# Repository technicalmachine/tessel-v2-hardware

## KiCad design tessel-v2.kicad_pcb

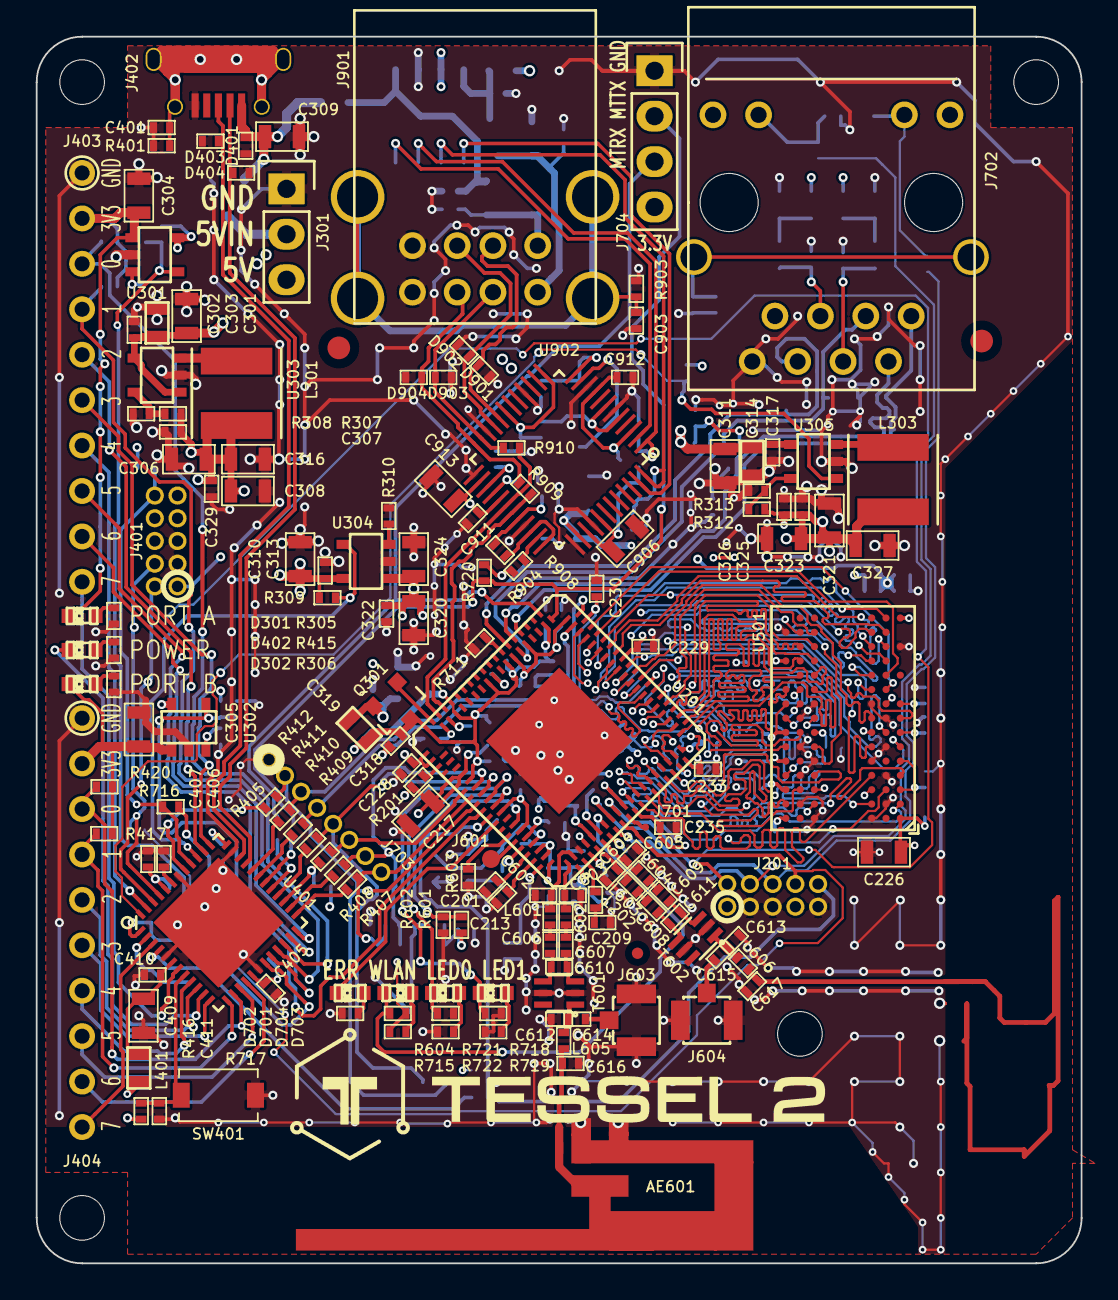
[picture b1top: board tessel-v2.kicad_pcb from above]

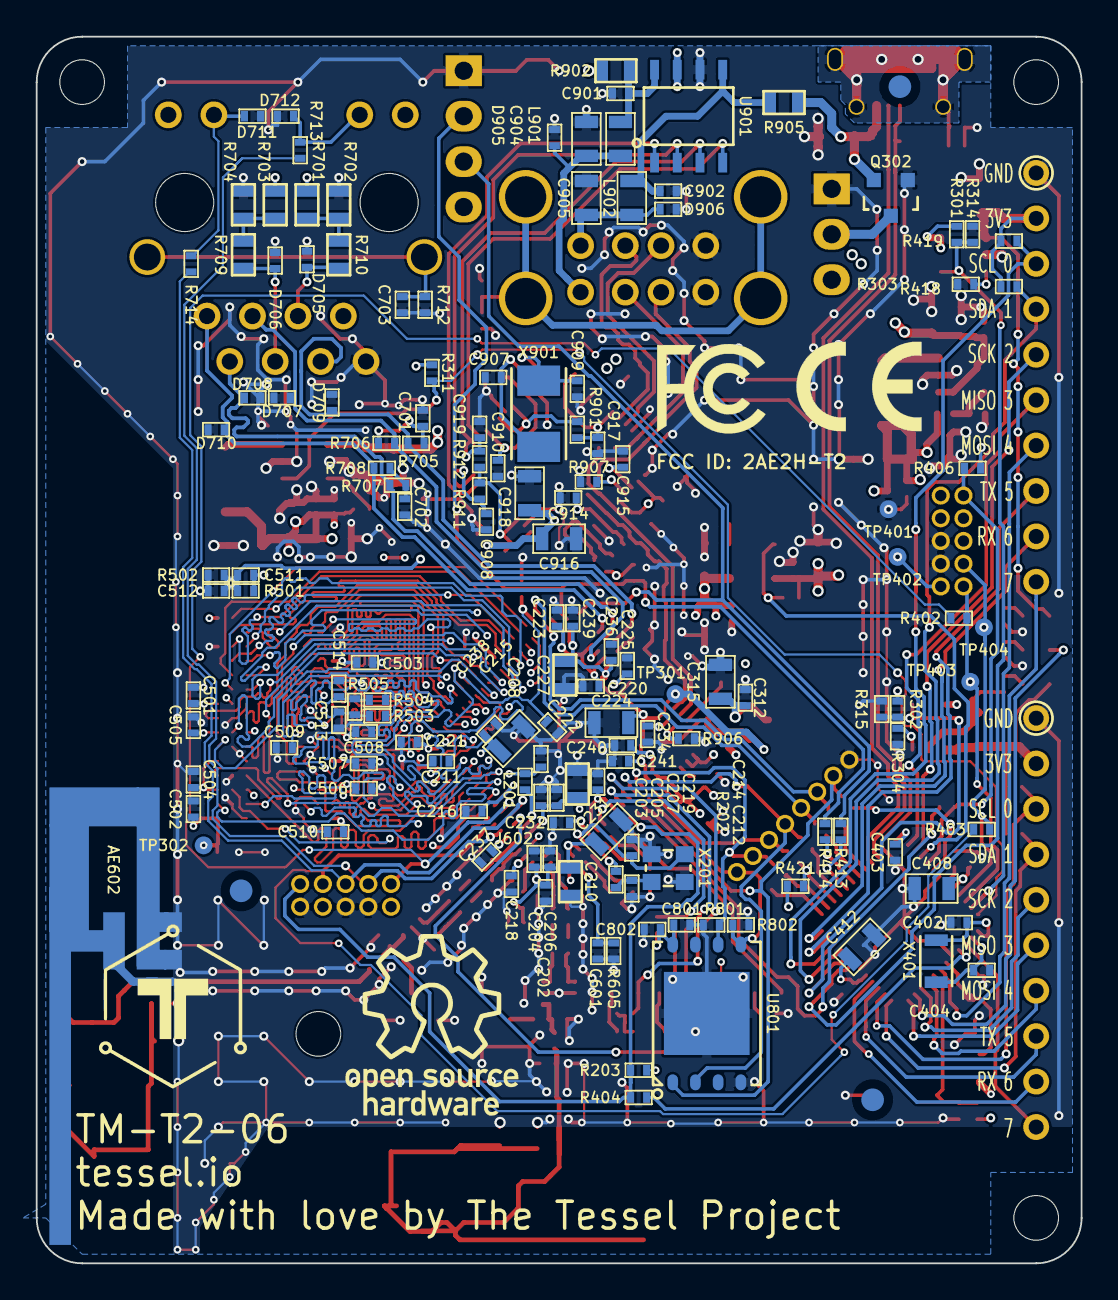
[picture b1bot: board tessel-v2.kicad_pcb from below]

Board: 4 copper layers, 58.4 x 68.6 mm, 315 parts (151 on the bottom side), 201 nets.

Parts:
AE601, AE602: ANTENNA; 2.4GHz-INVERTED-F-ANTENNA
C201, C208, C209, C220, C230, C238, C325, C329, C406, C908, C919: 1uF; SMD-0402-C
C202, C203, C204, C402, C404: 10pF; SMD-0402-C
C205, C206, C211, C216, C218, C219, C221, C222, C223, C225, C228, C229, C232, C233, C234, C235, C236, C237, C239, C240, C241, C307, C312, C318, C322, C326, C403, C405, C407, C410, C411, C502, C503, C504, C505, C507, C508, C509, C510, C511, C512, C701, C702, C801, C802, C901, C902, C910, C911, C912, C914, C915, C917: 100nF; SMD-0402-C
C207, C210, C227, C303, C314, C319: 4.7uF; SMD-0603-C
C212, C214, C907, C909: 18pF; SMD-0402-C
C213, C302, C313, C317, C501, C506: 10nF; SMD-0402-C
C215, C217, C224, C226, C308, C324, C327: 10uF DNP; SMD-0805-C
C231, C301, C304, C305, C306, C309, C310, C311, C315, C316, C320, C321, C323, C408, C409, C412, C904, C905, C906, C913, C916, C918: 10uF; SMD-0805-C
C401, C601, C606, C607, C608, C609, C703, C903: 100pF; SMD-0402-C
C513, C514: 5pF; SMD-0402-C
C602, C603, C604, C605: 2.2pF; SMD-0402-C
C610, C611: 0.8pF; SMD-0402-C
C612, C613, C616, C617: 1.8pF; SMD-0402-C
C614, C615: 100pF DNP; SMD-0402-C
D301, D302, D704: GREEN; LED-0603
D401, D403, D404, D901, D902, D903, D904, D905, D906: CV0402VT6030T; SMD-0402-R
D402, D703: BLUE; LED-0603
D701: AMBER; LED-0603
D702: RED; LED-0603
D705, D706, D707, D708, D709, D710, D711, D712: CV0402VT6001T; SMD-0402-R
F101, F102, F103, F104, F105, F106: fiducial
H101, H102, H103, H104: HOLE; MountingHole_2-5mm
J201, J401: CONN_02X05 DNP; CONN_02x05_0.05in
J301: CONN_01X03 DNP; Pin_Header_Straight_1x03
J402: MICROUSB-TH; Seeed-USB-Micro-320010028
J403, J404: MODULE_HEADER; MODULE_HEADER_TESSEL-backside
J601, J602, J701: CONN_01X01; Testpoint
J603, J604: UFL DNP; 1909763-1
J702: HR911105A; RB1-125BAG1A
J703: CONN_01X08 DNP; CONN_01x08_0.05in
J704: CONN_01X04 DNP; Pin_Header_Straight_1x04
J901: USB_A_2_stack; Molex-0672983090
L201, L202: 3.9nH; SMD-0402-R
L301, L303: 2.2uH; SWPA5020S
L401: 10uH; SMD-0603-R
L601, L602, L603, L604: 3nH; SMD-0402-R
L605, L606: 2.4nH; SMD-0402-R
L901, L902: BLM21PG221SN1D; SMD-0805-R
Q301: MMSS8550; SOT23
Q302: DMG2305UX; SOT-23
R201, R203, R417, R418, R419, R420, R601, R603, R720, R801, R802: 4.7kR; SMD-0402-R
R202, R404, R405, R407, R408, R409, R410, R411, R412, R413, R414, R503, R504, R716: 22R; SMD-0402-R
R301, R302: 100kR DNP; SMD-0402-R
R303, R304: 27kR; SMD-0402-R
R305, R306, R505, R722: 120R; SMD-0402-R
R307: 450kR 1%; SMD-0402-R
R308, R313: 100kR 1%; SMD-0402-R
R309, R310, R311, R406, R416, R421, R904, R908: 10kR; SMD-0402-R
R312: 200kR 1%; SMD-0402-R
R314, R315, R401, R604, R712, R718, R721, R901, R903: 100kR; SMD-0402-R
R402, R403, R713, R714, R715: 330R; SMD-0402-R
R415, R717, R719: 1kR; SMD-0402-R
R501, R502: 4.7kR 1%; SMD-0402-R
R602: 4.7kR DNP; SMD-0402-R
R605: 24kR 1%; SMD-0402-R
R701, R702, R703, R704: 10kR DNP; SMD-0603-R
R705, R706, R707, R708: 49.9R 1%; SMD-0402-R
R709, R710: 100kR DNP; SMD-0603-R
R711: 6.19kR 1%; SMD-0402-R
R902, R905: 0R DNP; SMD-0603-R
R906: 8.2kR 1%; SMD-0402-R
R907: 2.7kR 1%; SMD-0402-R
R909, R910: 0R DNP; SMD-0402-R
R911, R912: 450kR; SMD-0402-R
SILK101: Tessel 2 logo; TESSEL-TEXT-LOGO-31.8mm8.1mm
SILK102: OSHW logo; OSHW-Silk
SILK103: Tessel logo; Tessel-logo-10_2mm
SILK104: Tessel logo; LOGO-CE-5mm
SILK105: Tessel logo; LOGO-FCC-5mm
SW401: SW_PUSH; TL1015AF160QG
T601, T602: 2450BL15B100; EIA-0805
TP301, TP302, TP401, TP402, TP403, TP404: TP; Testpoint
U201: MT7620N
U301, U302, U304: MT9700; SOT-23-5
U303, U305: AP3418; SOT-23-5
U401: SAMD21G17A-MU; QFN-48-1EP-7mm
U501: W9751G6KB-25; WBGA-84
U801: S25FL256SAGNFI001; WNG008
U901: AIC1528-0PSTR; SOP-8
U902: FE1.1; CY7C65634-48AXCT
X201: 20MHz; CTS-425
X401: FC-135
X901: 12MHz; Seeed-xtal-12MHz

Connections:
3.3V_CP: C306.1, C307.1, C308.1, C310.1, C313.1, C316.1, C329.1, C403.1, C405.1, C407.1, C408.1, C412.1, J401.1, L301.1, L401.1, R301.1, R302.1, R307.1, R309.1, R406.2, R416.2, R421.2, TP402.~, U301.5, U302.5, U304.5, U401.17, U401.36, U401.44
3.3V_PORTA: C304.1, D301.2, J403.2, R418.2, R419.2, U301.1
3.3V_PORTB: C305.1, D302.2, J404.2, R417.2, R420.2, U302.1
12S_CTRL: Q301.1, U201.54
18V_EN: R311.2, U305.1, U401.48
+1.2V: C216.1, C219.1, C222.1, C224.1, C227.1, C230.1, C233.1, C236.1, C239.1, C241.1, C318.1, C319.1, Q301.3, TP301.~, U201.18, U201.25, U201.35, U201.51, U201.55, U201.84, U201.114, U201.120, U201.123, U201.128, U201.135, U201.140, U201.143
+1.8V: C215.1, C218.1, C221.1, C226.1, C229.1, C232.1, C235.1, C238.1, C312.1, C315.1, C318.2, C319.2, C321.1, C323.1, C325.1, C326.1, C327.1, C501.1, C502.1, C503.1, C504.1, C505.1, C506.1, C507.1, C508.1, C509.1, C510.1, C511.1, L303.1, Q301.2, R312.1, R501.2, TP302.~, U201.3, U201.10, U201.29, U201.93, U201.95, U201.144, U201.148, U501.A1, U501.A9, U501.C1, U501.C3, U501.C7, U501.C9, U501.E1, U501.E9, U501.G1, U501.G3, U501.G7, U501.G9, U501.J1, U501.J9, U501.M9, U501.R1
+3V3: C202.1, C203.1, C204.1, C205.1, C206.1, C207.1, C208.1, C209.1, C210.1, C217.1, C220.1, C223.1, C225.1, C228.1, C231.1, C234.1, C237.1, C240.1, C320.1, C322.1, C324.1, C801.1, C802.1, J201.1, J702.9, J702.12, J704.4, L201.1, L202.1, R201.2, R203.2, R311.1, R601.1, R604.1, R701.2, R703.2, R715.1, R720.1, R904.1, U201.1, U201.6, U201.56, U201.57, U201.60, U201.61, U201.79, U201.112, U201.117, U201.119, U201.122, U201.129, U201.134, U201.146, U201.147, U304.1, U801.8
+5V: C301.1, C302.1, C303.1, C309.1, C311.1, C314.1, C317.1, C916.1, C918.1, D401.1, J301.3, J402.1, Q302.2, R902.1, R905.1, U303.1, U303.4, U305.4, U901.7, U902.38
/COPROCESSOR/BUTTON: C411.1, R416.1, SW401.2, U401.8
/COPROCESSOR/CP_BRIDGE_MISO_SAM: R410.2, U401.28
/COPROCESSOR/CP_BRIDGE_MOSI_SAM: R407.2, U401.25
/COPROCESSOR/CP_BRIDGE_SAM_RX_SAM: R414.2, U401.30
/COPROCESSOR/CP_BRIDGE_SAM_TX_SAM: R413.2, U401.29
/COPROCESSOR/CP_BRIDGE_SCK_SAM: R408.2, U401.26
/COPROCESSOR/CP_BRIDGE_SCL_SAM: R412.2, U401.32
/COPROCESSOR/CP_BRIDGE_SDA_SAM: R411.2, U401.31
/COPROCESSOR/CP_BRIDGE_~CS~_SAM: R409.2, R421.1, U401.27
/COPROCESSOR/FLASH_~CS~_SAM: R405.1, U401.41
/COPROCESSOR/PORT_A_G1/TX: J403.8, U401.23
/COPROCESSOR/PORT_A_G2/RX: J403.9, U401.24
/COPROCESSOR/PORT_A_G3: J403.10, U401.7
/COPROCESSOR/PORT_A_MISO: J403.6, U401.37
/COPROCESSOR/PORT_A_MOSI: J403.7, U401.47
/COPROCESSOR/PORT_A_SCK: J403.5, U401.38
/COPROCESSOR/PORT_A_SCL: J403.3, R419.1, U401.22
/COPROCESSOR/PORT_A_SDA: J403.4, R418.1, U401.21
/COPROCESSOR/PORT_B_G1/TX: J404.8, U401.15
/COPROCESSOR/PORT_B_G2/RX: J404.9, U401.16
/COPROCESSOR/PORT_B_G3: J404.10, U401.3
/COPROCESSOR/PORT_B_MISO: J404.6, U401.12
/COPROCESSOR/PORT_B_MOSI: J404.7, U401.9
/COPROCESSOR/PORT_B_SCK: J404.5, U401.10
/COPROCESSOR/PORT_B_SCL: J404.3, R420.1, U401.14
/COPROCESSOR/PORT_B_SDA: J404.4, R417.1, U401.13
/COPROCESSOR/POWER_LED: D402.2, U401.11
/COPROCESSOR/SAM_USB_DM: D404.1, J402.2, U401.33
/COPROCESSOR/SAM_USB_DP: D403.1, J402.3, U401.34
/COPROCESSOR/SAM_USB_SHELL: C401.1, J402.6, J402.7, J402.8, J402.9, J402.10, J402.11, R401.1
/COPROCESSOR/SAM_XTAL32_1: C402.1, U401.1, X401.1
/COPROCESSOR/SAM_XTAL32_2: C404.1, U401.2, X401.2
/COPROCESSOR/VDDCORE: C406.1, U401.43
/COPROCESSOR/~PORST~_SAM: R404.1, U401.4
/MEDIATEK/MT_PLL_VC_CAP: C213.1, U201.73
/MEDIATEK/MT_XTAL_XI: C214.1, U201.145, X201.3
/MEDIATEK/MT_XTAL_XO: R202.1, U201.71
/MEDIATEK/MT_XTAL_XO_R: C212.1, R202.2, X201.1
/MEDIATEK/RF0_V33N: L201.2, U201.80
/MEDIATEK/RF1_V33N: L202.2, U201.2
/MEDIATEK_I/O/EPHY_RES: R711.1, U201.43
/MEDIATEK_I/O/ETH_LED_GREEN: D711.1, J702.11, R714.1
/MEDIATEK_I/O/ETH_LED_YELLOW: D712.1, J702.10, R713.1
/MEDIATEK_I/O/ETH_SHELL: C703.1, J702.13, J702.14, R712.1
/MEDIATEK_I/O/MT_GPIO_WP: R716.2, U201.65
/MEDIATEK_I/O/MT_~RESET: J701.1, U201.9
/MEDIATEK_I/O/RM: C701.1, R705.1, R706.1
/MEDIATEK_I/O/RN_P1: D709.1, J702.6, R705.2, U201.42
/MEDIATEK_I/O/RP_P1: D707.1, J702.3, R706.2, U201.118
/MEDIATEK_I/O/RXM: R701.1, R702.2, R710.2
/MEDIATEK_I/O/RX_MIDTAP: D705.1, J702.5, R710.1
/MEDIATEK_I/O/TM: C702.1, R707.1, R708.1
/MEDIATEK_I/O/TN_P1: D708.1, J702.2, R707.2, U201.41
/MEDIATEK_I/O/TP_P1: D710.1, J702.1, R708.2, U201.40
/MEDIATEK_I/O/TXM: R703.1, R704.2, R709.2
/MEDIATEK_I/O/TX_MIDTAP: D706.1, J702.4, R709.1
/MEDIATEK_I/O/USER_LED_BLUE: D703.2, R718.1, U201.138
/MEDIATEK_I/O/USER_LED_GREEN: D704.2, R721.1, U201.139
/POWER/5V_IN: J301.2, Q302.3
/POWER/18S_FB: R312.2, R313.1, U305.5
/POWER/18S_SW: L303.2, U305.3
/POWER/33C_FB: R307.2, R308.1, U303.5
/POWER/33C_SW: L301.2, U303.3
/RAM/A0: U201.20, U501.M8
/RAM/A1: U201.107, U501.M3
/RAM/A2: U201.96, U501.M7
/RAM/A3: U201.31, U501.N2
/RAM/A4: U201.21, U501.N8
/RAM/A5: U201.106, U501.N3
/RAM/A6: U201.97, U501.N7
/RAM/A7: U201.30, U501.P2
/RAM/A8: U201.22, U501.P8
/RAM/A9: U201.104, U501.P3
/RAM/A10: U201.32, U501.M2
/RAM/A11: U201.98, U501.P7
/RAM/A12: U201.105, U501.R2
/RAM/BA0: U201.33, U501.L2
/RAM/BA1: U201.108, U501.L3
/RAM/CKE: U201.34, U501.K2
/RAM/DDR2_CLK: C513.1, R503.1, R505.1, U501.J8
/RAM/DQ0: U201.24, U501.G8
/RAM/DQ1: U201.26, U501.G2
/RAM/DQ2: U201.99, U501.H7
/RAM/DQ3: U201.27, U501.H3
/RAM/DQ4: U201.102, U501.H1
/RAM/DQ5: U201.23, U501.H9
/RAM/DQ6: U201.101, U501.F1
/RAM/DQ7: U201.100, U501.F9
/RAM/DQ8: U201.88, U501.C8
/RAM/DQ9: U201.11, U501.C2
/RAM/DQ10: U201.87, U501.D7
/RAM/DQ11: U201.12, U501.D3
/RAM/DQ12: U201.86, U501.D1
/RAM/DQ13: U201.13, U501.D9
/RAM/DQ14: U201.85, U501.B1
/RAM/DQ15: U201.14, U501.B9
/RAM/DQM0: U201.28, U501.F3
/RAM/DQM1: U201.15, U501.B3
/RAM/DQS0: U201.103, U501.F7
/RAM/DQS1: U201.89, U501.B7
/RAM/M_DDR2_CLK: R503.2, U201.90
/RAM/M_~DDR2_CLK: R504.2, U201.16
/RAM/ODT: U201.17, U501.K9
/RAM/~CAS: U201.19, U501.L7
/RAM/~CS: U201.94, U501.L8
/RAM/~DDR2_CLK: C514.1, R504.1, R505.2, U501.K8
/RAM/~RAS: U201.92, U501.K7
/RAM/~WE: U201.109, U501.K3
/RF/ANT_TRN: R601.2, R602.2, U201.142
/RF/ANT_TRNB: R603.2, U201.69
/RF/NC_70: J601.1, U201.70
/RF/NC_78: J602.1, U201.78
/RF/RF0_BALUN_IN_N: C606.1, C610.1, T601.4
/RF/RF0_BALUN_IN_P: C607.1, C610.2, T601.3
/RF/RF0_BALUN_OUT: C612.1, C614.2, L605.2, T601.1
/RF/RF0_FEED: AE601.1, C616.1, L605.1
/RF/RF0_OUTN: C602.1, L601.2, U201.76
/RF/RF0_OUTN_TCIN: C606.2, L601.1
/RF/RF0_OUTP: C603.1, L602.2, U201.75
/RF/RF0_OUTP_TCIN: C607.2, L602.1
/RF/RF1_BALUN_IN_N: C609.1, C611.2, T602.3
/RF/RF1_BALUN_IN_P: C608.1, C611.1, T602.4
/RF/RF1_BALUN_OUT: C613.1, C615.2, L606.2, T602.1
/RF/RF1_FEED: AE602.1, C617.1, L606.1
/RF/RF1_OUTN: C605.1, L604.2, U201.5
/RF/RF1_OUTN_TCIN: C609.2, L604.1
/RF/RF1_OUTP: C604.1, L603.2, U201.4
/RF/RF1_OUTP_TCIN: C608.2, L603.1
/RF/UFL_0: C614.1, J603.1
/RF/UFL_1: C615.1, J604.1
/USB/33_USB: C906.1, C914.1, C915.1, C917.1, R901.1, R908.1, R911.1, R912.1, U902.13, U902.19, U902.27, U902.32, U902.39, U902.41
/USB/OVR#[1]: C908.1, R911.2, U901.2, U902.48
/USB/OVR#[2]: C919.1, R912.2, U901.3, U902.1
/USB/OVR#[3]: R901.2, U902.5, U902.7
/USB/PWR#[1]: U901.1, U902.47
/USB/PWR#[2]: U901.4, U902.2
/USB/UPHY0_PADM: R910.1, U201.53, U902.30
/USB/UPHY0_PADP: R909.1, U201.52, U902.31
/USB/UPHY0_VRES: R906.1, U201.130
/USB/USB_18: C910.1, C911.1, C912.1, C913.1, U902.3, U902.9, U902.26, U902.29
/USB/USB_DD+[1]: D904.1, J901.3, R909.2, U902.24
/USB/USB_DD+[2]: D902.1, J901.7, U902.21
/USB/USB_DD-[1]: D903.1, J901.2, R910.2, U902.23
/USB/USB_DD-[2]: D901.1, J901.6, U902.20
/USB/USB_PU: R908.2, U902.34, U902.36
/USB/USB_RREF: R907.1, U902.28
/USB/USB_XTAL_IN: C909.1, U902.12, X901.2
/USB/USB_XTAL_OUT: C907.1, U902.11, X901.1
/USB/VBUSM: R904.2, U902.35
/USB/VBUS[1]: C904.1, D905.1, J901.1, L901.1
/USB/VBUS[1]_IN: C901.1, L901.2, R902.2, U901.8
/USB/VBUS[2]: C905.1, D906.1, J901.5, L902.1
/USB/VBUS[2]_IN: C902.1, L902.2, R905.2, U901.5
CP_BRIDGE_MISO: J703.5, R410.1, U201.137, U801.2
CP_BRIDGE_MOSI: J703.8, R407.1, R802.1, U201.63, U801.5
CP_BRIDGE_SAM_RX: J704.2, R414.1, R720.2, U201.113
CP_BRIDGE_SAM_TX: J704.3, R413.1, U201.37
CP_BRIDGE_SCK: J703.7, R408.1, R801.1, U201.136, U801.6
CP_BRIDGE_SCL: J703.3, R412.1, U201.111
CP_BRIDGE_SDA: J703.4, R411.1, U201.36
CP_BRIDGE_~CS: J703.6, R409.1, U201.62
CP_VDDANA: C409.1, C410.1, L401.2, U401.6
DDR_VREF: C211.1, C511.2, C512.1, R501.1, R502.2, U201.91, U201.110, U501.J2
ERROR_LED: D702.2, U201.67
FLASH_~CS: J703.2, R405.2, U201.64, U801.1
GND: AE601.2, AE602.2, C201.2, C202.2, C203.2, C204.2, C205.2, C206.2, C207.2, C208.2, C209.2, C210.2, C211.2, C212.2, C213.2, C214.2, C215.2, C216.2, C217.2, C218.2, C219.2, C220.2, C221.2, C222.2, C223.2, C224.2, C225.2, C226.2, C227.2, C228.2, C229.2, C230.2, C231.2, C232.2, C233.2, C234.2, C235.2, C236.2, C237.2, C238.2, C239.2, C240.2, C241.2, C301.2, C302.2, C303.2, C304.2, C305.2, C306.2, C307.2, C308.2, C309.2, C310.2, C311.2, C312.2, C313.2, C314.2, C315.2, C316.2, C317.2, C320.2, C321.2, C322.2, C323.2, C324.2, C325.2, C326.2, C327.2, C329.2, C401.2, C402.2, C403.2, C404.2, C405.2, C406.2, C407.2, C408.2, C409.2, C410.2, C411.2, C412.2, C501.2, C502.2, C503.2, C504.2, C505.2, C506.2, C507.2, C508.2, C509.2, C510.2, C512.2, C513.2, C514.2, C601.2, C602.2, C603.2, C604.2, C605.2, C612.2, C613.2, C616.2, C617.2, C701.2, C702.2, C703.2, C801.2, C802.2, C901.2, C902.2, C903.2, C904.2, C905.2, C906.2, C907.2, C908.2, C909.2, C910.2, C911.2, C912.2, C913.2, C914.2, C915.2, C916.2, C917.2, C918.2, C919.2, D401.2, D403.2, D404.2, D705.2, D706.2, D707.2, D708.2, D709.2, D710.2, D711.2, D712.2, D901.2, D902.2, D903.2, D904.2, D905.2, D906.2, J201.3, J201.5, J201.9, J301.1, J401.3, J401.5, J402.5, J403.1, J404.1, J603.2, J603.3, J604.2, J604.3, J702.8, J703.1, J704.1, J901.4, J901.8, Q302.1, R303.2, R304.2, R305.2, R306.2, R308.2, R310.2, R313.2, R314.2, R315.2, R401.2, R415.1, R502.1, R602.1, R603.1, R605.1, R702.1, R704.1, R711.2, R712.2, R717.1, R718.2, R719.2, R721.2, R722.2, R801.2, R802.2, R903.2, R906.2, R907.2, SW401.1, T601.2, T601.5, T602.2, T602.5, TP401.~, U201.77, U201.149, U301.2, U302.2, U303.2, U304.2, U305.2, U401.5, U401.18, U401.35, U401.42, U401.49, U501.A3, U501.A7, U501.B2, U501.B8, U501.D2, U501.D8, U501.E3, U501.E7, U501.F2, U501.F8, U501.H2, U501.H8, U501.J3, U501.J7, U501.N1, U501.P9, U801.4, U801.9, U901.6, U902.6, U902.10, U902.16, U902.22, U902.25, U902.33, U902.37, U902.40, X201.2, X201.4
MT_PWR_EN: R309.2, U304.4, U401.39
MT_TCLK: J201.4, R713.2, U201.7
MT_TDI: J201.8, R403.1, U201.8
MT_TDO: J201.6, R714.2, U201.82
MT_TMS: J201.2, R402.1, U201.83
unnamed: C201.1, U201.72
unnamed: C601.1, R605.2, U201.74
unnamed: C903.1, J901.9, J901.10, J901.11, J901.12, R903.1
unnamed: D301.1, R305.1
unnamed: D302.1, R306.1
unnamed: D402.1, R415.2
unnamed: D701.2, R715.2
unnamed: D702.1, R717.2
unnamed: D703.1, R719.1
unnamed: D704.1, R722.1
unnamed: R201.1, U201.58
unnamed: R303.1, U301.3
unnamed: R304.1, U302.3
unnamed: R310.1, U304.3
PORT_A_PWR_EN: R301.2, R314.1, U301.4, U401.19
PORT_B_PWR_EN: R302.2, R315.1, U302.4, U401.20
SAM_~RESET: J401.10, R406.1, R716.1, U401.40
SWCLK: J401.4, R403.2, TP404.~, U401.45
SWDIO: J401.2, R402.2, TP403.~, U401.46
~PORST: J201.10, R203.1, R404.2, U201.66
~WLAN~_LED: D701.1, R604.2, U201.81

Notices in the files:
tessel-v2.kicad_pcb:
Copyright 2015 Technical Machine Inc.
CC-BY-SA or Solderpad, at your option.
